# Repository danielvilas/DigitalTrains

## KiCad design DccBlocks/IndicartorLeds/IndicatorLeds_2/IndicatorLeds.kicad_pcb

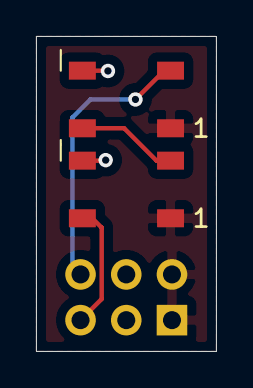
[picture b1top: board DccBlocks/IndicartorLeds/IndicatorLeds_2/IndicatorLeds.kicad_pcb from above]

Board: 2 copper layers, 10.0 x 17.5 mm, 3 parts (1 on the bottom side), 5 nets.

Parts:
D1, D2: WS2812B; LED_WS2812B_PLCC4_5.0x5.0mm_P3.2mm
J1: Conn_02x03_Odd_Even; PinHeader_2x03_P2.54mm_Vertical

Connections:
/Din: D1.4, J1.5
/Dout: D2.2, J1.6
GND: D1.3, D2.3, J1.3, J1.4
unnamed: D1.2, D2.4
VCC: D1.1, D2.1, J1.1, J1.2

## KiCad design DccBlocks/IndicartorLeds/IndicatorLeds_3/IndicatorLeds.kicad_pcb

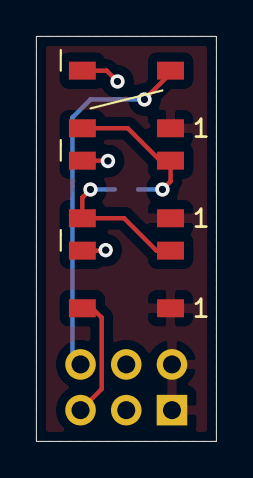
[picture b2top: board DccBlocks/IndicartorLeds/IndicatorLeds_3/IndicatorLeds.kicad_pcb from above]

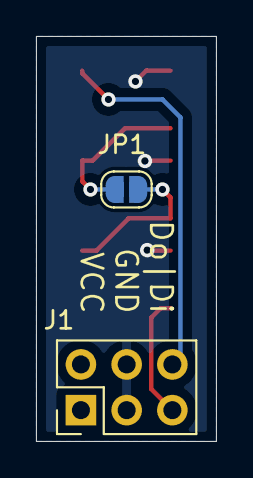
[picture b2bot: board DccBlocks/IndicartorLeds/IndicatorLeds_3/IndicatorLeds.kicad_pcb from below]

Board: 2 copper layers, 10.0 x 22.5 mm, 5 parts (2 on the bottom side), 6 nets.

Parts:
D1, D2, D3: WS2812B; LED_WS2812B_PLCC4_5.0x5.0mm_P3.2mm
J1: Conn_02x03_Odd_Even; PinHeader_2x03_P2.54mm_Vertical
JP1: MiddleBypass; SolderJumper-2_P1.3mm_Open_RoundedPad1.0x1.5mm

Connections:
/Din: D1.4, J1.5
/Dout: D3.2, J1.6
GND: D1.3, D2.3, D3.3, J1.3, J1.4
unnamed: D1.2, D2.4, JP1.1
unnamed: D2.2, D3.4, JP1.2
VCC: D1.1, D2.1, D3.1, J1.1, J1.2

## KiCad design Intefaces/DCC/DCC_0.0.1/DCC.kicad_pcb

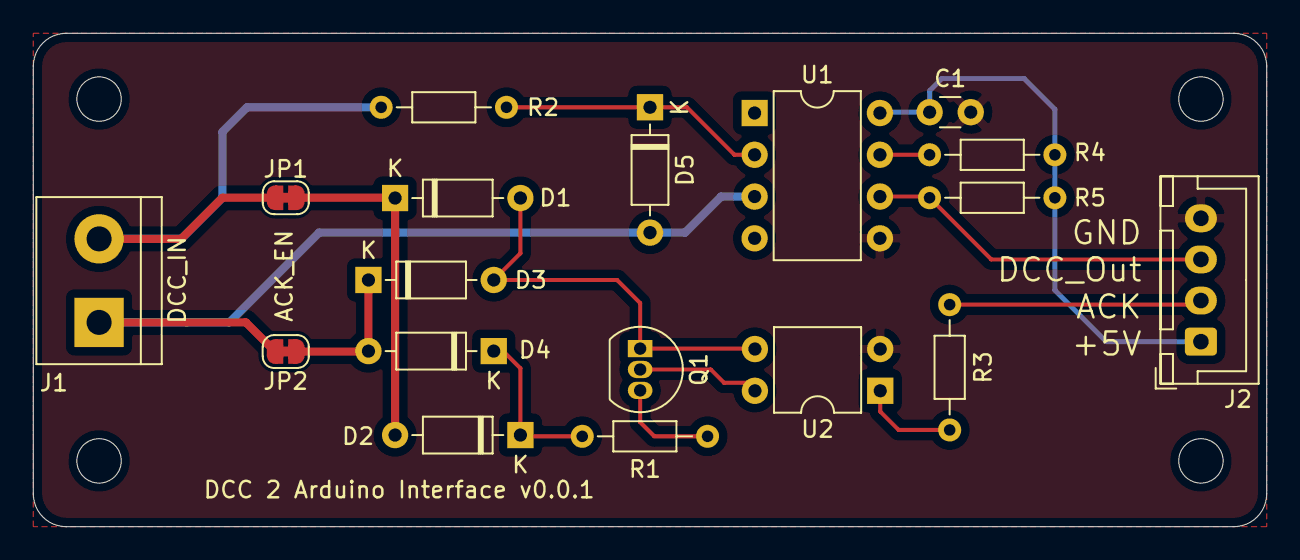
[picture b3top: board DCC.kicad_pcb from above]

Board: 2 copper layers, 75.0 x 30.0 mm, 22 parts (0 on the bottom side), 15 nets.

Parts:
C1: 100uf; C_Disc_D3.0mm_W1.6mm_P2.50mm
D1, D2, D3, D4, D5: 1N4148; D_DO-35_SOD27_P7.62mm_Horizontal
H1, H2, H3, H4: MountingHole; MountingHole_2.7mm_M2.5
J1: Screw_Terminal_01x02; TerminalBlock_bornier-2_P5.08mm
J2: Conn_01x04; JST_XH_B4B-XH-A_1x04_P2.50mm_Vertical
JP1, JP2: Jumper_NC_Small; SolderJumper-2_P1.3mm_Bridged_RoundedPad1.0x1.5mm
Q1: BC560; TO-92_Inline
R1: 100; R_Axial_DIN0204_L3.6mm_D1.6mm_P7.62mm_Horizontal
R2: 3k9; R_Axial_DIN0204_L3.6mm_D1.6mm_P7.62mm_Horizontal
R3: 1K; R_Axial_DIN0204_L3.6mm_D1.6mm_P7.62mm_Horizontal
R4, R5: 10k; R_Axial_DIN0204_L3.6mm_D1.6mm_P7.62mm_Horizontal
U1: 6N137; DIP-8_W7.62mm
U2: PC817; DIP-4_W7.62mm

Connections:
/DCC_IN: J2.3, R5.1, U1.6
/J: J1.2, JP1.2, R2.2
/J_ACK: D1.1, D2.2, JP1.1
/K: D5.2, J1.1, JP2.2, U1.3
/K_ACK: D3.1, D4.2, JP2.1
/ack: J2.2, R3.1
GND: C1.2, J2.4, U1.5, U2.2
unnamed: D1.2, D3.2, Q1.1, U2.3
unnamed: D2.1, D4.1, R1.2
unnamed: D5.1, R2.1, U1.2
unnamed: Q1.2, U2.4
unnamed: Q1.3, R1.1
unnamed: R3.2, U2.1
unnamed: R4.1, U1.7
VCC: C1.1, J2.1, R4.2, R5.2, U1.8

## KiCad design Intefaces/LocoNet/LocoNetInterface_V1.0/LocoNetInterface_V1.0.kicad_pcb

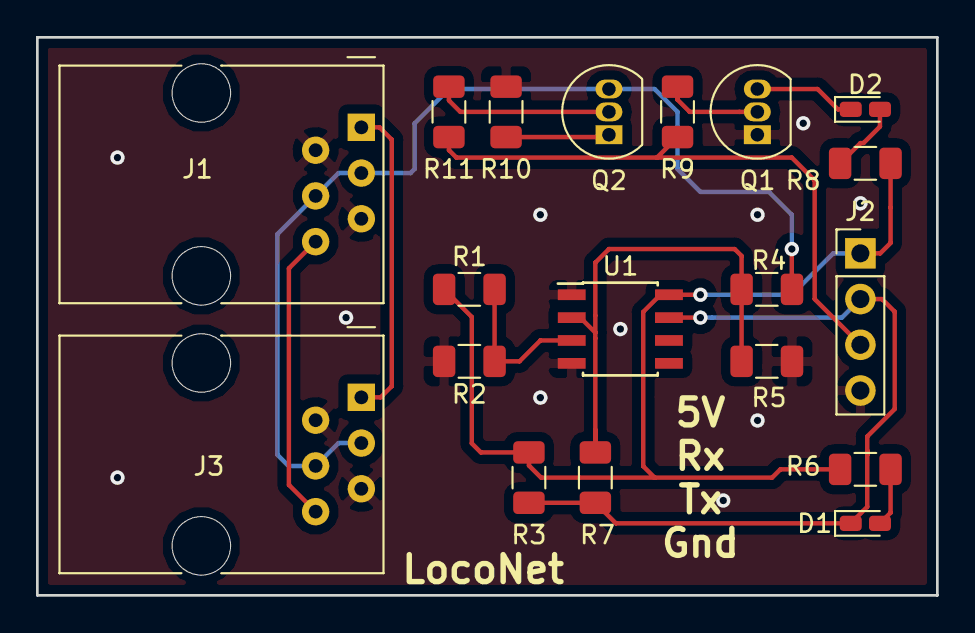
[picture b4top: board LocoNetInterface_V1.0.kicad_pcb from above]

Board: 2 copper layers, 50.0 x 31.0 mm, 19 parts (0 on the bottom side), 15 nets.

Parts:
D1, D2: LED; LED_0603_1608Metric_Castellated
J1, J3: RJ12; RJ12_Amphenol_54601
J2: Conn_01x04; PinHeader_1x04_P2.54mm_Vertical
Q1, Q2: 2N3904; TO-92_Inline
R1: 10K; R_1206_3216Metric
R2: 22K; R_1206_3216Metric
R3: 1K; R_1206_3216Metric
R4: 47K; R_1206_3216Metric
R5: 150K; R_1206_3216Metric
R6, R8: 470; R_1206_3216Metric
R7: 220K; R_1206_3216Metric
R9, R11: 4.7K; R_1206_3216Metric
R10: 47; R_1206_3216Metric
U1: LM311; SOIC-8_3.9x4.9mm_P1.27mm

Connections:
+5V: J2.1, R1.1, R3.2, R6.2, R8.2, U1.8
/RX: D1.1, J2.2, R3.1, R7.1, U1.7
/TX: J2.3, R9.1, R11.1
/loconet: J1.3, J1.4, J3.3, J3.4, Q2.3, R4.1
GND: J1.2, J1.5, J2.4, J3.2, J3.5, Q1.1, R2.2, R5.2, R10.1, U1.1, U1.4
unnamed: D1.2, R6.1
unnamed: D2.1, Q1.3
unnamed: D2.2, R8.1
unnamed: J1.1, J3.1
unnamed: J1.6, J3.6
unnamed: Q1.2, R9.2
unnamed: Q2.1, R10.2
unnamed: Q2.2, R11.2
unnamed: R1.2, R2.1, U1.3
unnamed: R4.2, R5.1, R7.2, U1.2
